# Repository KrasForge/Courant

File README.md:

# RADIAN

<p align="center">
  <a href="#listen"><b>Listen</b></a> ·
  <a href="#see-the-mesh-move"><b>See the mesh move</b></a> ·
  <a href="#the-hardware"><b>Hardware & 3D</b></a> ·
  <a href="#1-mathematical-foundation"><b>The maths</b></a> ·
  <a href="#4-architecture"><b>Architecture</b></a>
</p>

A 2D finite-difference physical-modeling synthesis engine in structural VHDL,
with an amplitude-dependent non-linear "chaos injection" term, playable
polyphonically over MIDI or CV.

Instead of recording or sampling an instrument, RADIAN solves the 2D acoustic
wave equation in real time on an FPGA mesh of arithmetic cells and streams the
result out as stereo audio: a vibrating drum head, a plate, a sheet of metal,
*computed* rather than recorded. A non-linear tension term makes the mesh
stiffen under load, so hard hits bend pitch upward and bloom into inharmonic,
metallic partials before settling into a natural decay. Notes arrive over MIDI
or control voltage, are allocated across independent polyphonic voices, and are
shaped by recallable instrument presets and a live front panel.

<sub>RADIAN was developed as **Courant**, which is why the repository and
some file paths still use that name.</sub>

> **Status: simulation-first, feature-complete in simulation, pre-hardware.**
> The engine, a Q1.23 reference model that is *bit-exact* to the RTL, and a full
> playable top (MIDI/CV $\rightarrow$ polyphony $\rightarrow$ I2S audio) are
> developed and verified under the current RTL regression across 31 testbenches. Board bring-up on a
> Digilent Arty A7 + Pmod I2S2 is the next step; nothing is claimed to work on
> hardware until it does.

---

## Listen

These clips come **out of the RTL**. A cycle-accurate Verilator build of
`synth_top` (4 voices, 8 $\times$ 8 mesh, 4$\times$ oversampling,
time-multiplexed) receives the score as bit-level serial MIDI at 31250 baud.
The note mapping, voice allocation, polyphonic meshes, mixer, DC blocker,
clock-domain crossing and I2S serialiser all run in it, and its 24-bit I2S
output is captured. Each clip gets one constant gain to peak at −1 dBFS. There
is no EQ, compression, reverb or editing. **They are not hardware
recordings**: the FPGA has not been brought up yet. Click a spectrogram or a ▶
link and the clip plays in your browser.

| Clip | What you hear | Listen |
| --- | --- | --- |
| **Gong Chorale** | A-minor chord progression on the gong preset. 3–4 voices ring into each other | [▶ `rtl_gong_chorale.mp3`](https://cdn.jsdelivr.net/gh/KrasForge/Courant@a1daff8e3a3599e712c28fc31fcfe1d983a12df5/docs/media/audio/rtl_gong_chorale.mp3) · 13 s |
| **Chaos Swell** | One held gong chord while CHAOS is turned up live over the control bus and back down | [▶ `rtl_chaos_swell.mp3`](https://cdn.jsdelivr.net/gh/KrasForge/Courant@a1daff8e3a3599e712c28fc31fcfe1d983a12df5/docs/media/audio/rtl_chaos_swell.mp3) · 12 s |
| **Plate Arpeggio** | Rolling pentatonic arpeggios on the plate preset with overlapping held notes, 112 BPM | [▶ `rtl_plate_arpeggio.mp3`](https://cdn.jsdelivr.net/gh/KrasForge/Courant@a1daff8e3a3599e712c28fc31fcfe1d983a12df5/docs/media/audio/rtl_plate_arpeggio.mp3) · 11 s |
| **Mallet Groove** | Marimba-like line on the damped drum preset over a held bass, 120 BPM | [▶ `rtl_mallet_groove.mp3`](https://cdn.jsdelivr.net/gh/KrasForge/Courant@a1daff8e3a3599e712c28fc31fcfe1d983a12df5/docs/media/audio/rtl_mallet_groove.mp3) · 10 s |
| **Berlin Voltage** | Dry EBM / industrial pulse, 132 BPM | [▶ `rtl_berlin_voltage.mp3`](https://cdn.jsdelivr.net/gh/KrasForge/Courant@f79031551d7316b354aa7c6243a771c9426d3952/docs/media/audio/rtl_berlin_voltage.mp3) · 10 s |
| **Oxide Dub** | Free-boundary metallic dub with long tails, 96 BPM | [▶ `rtl_oxide_dub.mp3`](https://cdn.jsdelivr.net/gh/KrasForge/Courant@f79031551d7316b354aa7c6243a771c9426d3952/docs/media/audio/rtl_oxide_dub.mp3) · 10 s |
| **Kreuz Rhythm** | Metallic polyrhythm with a tense finish, 150 BPM | [▶ `rtl_kreuz_rhythm.mp3`](https://cdn.jsdelivr.net/gh/KrasForge/Courant@f79031551d7316b354aa7c6243a771c9426d3952/docs/media/audio/rtl_kreuz_rhythm.mp3) · 10 s |

<sub>Rendered from the repaired RTL of 2026-09-16, the build behind
[`docs/sound_engine_repair.md`](docs/sound_engine_repair.md). It predates the
FX chain (drive, delay, chorus, reverb), the physical mallet and plate
stiffness, so these clips are the dry resonator. The scores are in
[`docs/media/scores/`](docs/media/scores/), and
[`make_scores.py`](docs/media/scripts/rtl/make_scores.py) writes the first
four. Rebuild the renderer from the
current RTL with
[`docs/media/scripts/rtl/build_renderer.sh`](docs/media/scripts/rtl/build_renderer.sh);
the whole 100 MHz system clock is simulated, so expect several minutes of CPU
per second of audio. Each clip also has an `.mp4` (spectrogram with a moving
playhead) in [`docs/media/audio/`](docs/media/audio/).</sub>

### Chaos off vs. chaos on

This one illustrates the non-linearity in the float reference model
([`model/NLMesh2D.m`](model/NLMesh2D.m), the same update as the RTL) on a
32 $\times$ 32 mesh. The same centre strike on the same gong mesh, first linear
($\alpha = 0$), then with chaos injection ($\alpha = 0.42$). The linear mesh
rings as a clean stack of fixed modes. With the amplitude-dependent term,
energy smears across the band right after the hit and the partials bend as the
mesh relaxes.

The flat ceiling near 5 kHz is not a filter. It is the highest mode a 2D
mesh can carry, $f_{\max} = \tfrac{f_s}{\pi}\arcsin(\gamma\sqrt{2}) \approx 4.9$ kHz
for this gong's $\gamma^2 = 0.05$. A finer mesh for the same pitch raises
$\gamma$ and lifts it.

### See the mesh move

The same hard strike on both meshes, slowed down about 800 $\times$. On the
left the wavefront spreads at one speed. On the right the loud centre
stiffens, so it runs ahead and breaks into fine, high-frequency ripples:
those ripples are the inharmonic partials you hear.

---

## The hardware

The engine targets a two-board desktop/Eurorack instrument. A 160 $\times$ 100 mm,
six-layer **Artix-7 mainboard** (FPGA, flash, clocks, PCM5102A DAC, CV/pot ADC,
opto-isolated MIDI) carries a **panel/interface board** 19.99 mm above it on
two 20-pin Samtec mezzanines. The panel has six knobs (TENSION · DECAY ·
CHAOS large, DRIVE · DELAY · REVERB small), a push encoder, the MODE switch,
four LEDs and five patch jacks. Neither board has been fabricated yet. See
[`hardware/CURRENT_DESIGN.md`](hardware/CURRENT_DESIGN.md) for what is and is
not validated.

<p align="center">
  <br>
  <sub>The two boards out of the case: the panel/interface board mated 19.99 mm above the Artix-7 mainboard.</sub>
</p>

<p align="center">
  <br>
  <sub>See-through view of the desktop case with both boards and the actual-part 3D models inside, rendered from
  the STEP assembly described in <a href="hardware/CURRENT_DESIGN.md"><code>hardware/CURRENT_DESIGN.md</code></a>
  (the STEP files themselves are not committed). The case has not been built yet.</sub>
</p>

| Mainboard (top) | Panel / interface board (front) |
| --- | --- |
|  |  |
|  |  |

<p align="center">
  <br>
  <sub>Side view of the stack. The mainboard's Samtec IPT1 posts reach into the panel's IPS1 sockets; the FPGA shows through the panel window.</sub>
</p>

**Open the 3D model:** [`courant_stack.stl`](docs/media/3d/courant_stack.stl)
opens in GitHub's built-in 3D viewer, so you can orbit it in the browser. The
coloured glTF files ([stack](docs/media/3d/courant_stack.glb),
[mainboard](docs/media/3d/courant_mainboard.glb),
[panel](docs/media/3d/courant_panel.glb)) open in any glTF viewer, Blender, or
https://gltf-viewer.donmccurdy.com.

<sub>Every outline, drill, pad, track and component position is read straight
from the native KiCad 10 boards. Component bodies are simplified parametric
stand-ins sized from package datasheets, and the knobs are illustrative. The
full actual-part STEP assembly lives outside the repo, so treat these as
layout previews, not mechanical CAD. Regenerate everything with
[`docs/media/scripts/make_media.sh`](docs/media/scripts/make_media.sh).</sub>

---

## Why an FPGA

A 2D mesh is embarrassingly parallel: every node runs the *same* small update
every time step, reading only its four neighbours. That maps naturally onto FPGA
fabric, where many nodes update concurrently and the per-sample cost does not
grow the way a sequential `for`-loop over the grid does on a CPU.

The honest trade is real, and this README states it plainly rather than selling
a fantasy:

| Aspect | Software (CPU / plugin) | This FPGA engine |
| --- | --- | --- |
| **Grid scaling** | Sequential per node; cost grows with node count | Concurrent nodes; one mesh step per audio sample, independent of node count (up to the fabric's DSP/LUT budget) |
| **Latency** | Governed by the host audio buffer (roughly 0.7 to 6 ms typical) | Deterministic, sub-sample; no block buffering. Group delay through the model is the physical wave propagation itself |
| **Per-node non-linearity** | Often simplified or dropped to save CPU | Evaluated on every node, every step |
| **Iteration speed** | Edit, recompile in seconds | Requires re-synthesis (minutes); behaviour bounded by chosen fabric |
| **Cost / footprint** | Runs on hardware you already own | Needs an FPGA plus an audio codec; each extra voice consumes finite DSP/LUT |

FPGAs win on **deterministic parallelism and latency**. Software wins on
**flexibility and cost**. This project is about the former.

---

## 1. Mathematical foundation

The engine models a lossy 2D wave equation for the transverse displacement
$u(x, y, t)$ of the surface:

$$\frac{\partial^2 u}{\partial t^2} = c^2\left(\frac{\partial^2 u}{\partial x^2} + \frac{\partial^2 u}{\partial y^2}\right) - 2\sigma\frac{\partial u}{\partial t}$$

- $c$ is the wave propagation speed (sets pitch and tension);
- $\sigma$ is the frequency-independent damping (sets decay time).

### Discretisation

Using centred finite differences on a grid with spacing $h$ and time step
$k = 1/f_s$ (with $f_s$ the audio rate, e.g. 48 kHz), the explicit update for
node $(i, j)$ is:

$$u_{i,j}^{n+1} = \frac{1}{1+\sigma k}\left[\,2u_{i,j}^{n} - (1-\sigma k)\,u_{i,j}^{n-1} + \gamma^2\left(u_{i+1,j}^{n} + u_{i-1,j}^{n} + u_{i,j+1}^{n} + u_{i,j-1}^{n} - 4u_{i,j}^{n}\right)\right]$$

where $\gamma = ck/h$ is the **Courant number**. The bracketed Laplacian stencil
is the only inter-node coupling; everything else is local. In the RTL the two
damping coefficients are precomputed on the control bus,

$$a_0 = \frac{1}{1+\sigma k}, \qquad \mathrm{sigk1} = 1 - \sigma k,$$

so no node ever performs a division (division is expensive in fabric; this
avoids it entirely).

### Stability (CFL), and why it is the whole game here

An explicit 2D scheme is only stable when the Courant number satisfies

$$\gamma^2 \le \tfrac{1}{2}\qquad\left(\gamma \le \tfrac{1}{\sqrt 2}\approx 0.7071\right).$$

Cross that line and the scheme does not merely "sound bad," it diverges
**exponentially**. This constraint governs every design decision in the next
section.

---

## 2. The non-linear twist: chaos injection

A linear mesh with a constant $\gamma$ is predictable and, frankly, a bit
sterile. RADIAN makes the local Courant term **amplitude-dependent**, so the
mesh stiffens where it is moving hardest:

$$\gamma_{i,j}^2 = \gamma_0^2 + \alpha\,(u_{i,j}^{n})^2$$

- $\gamma_0^2$ is the base stiffness and pitch;
- $\alpha$ is the chaos coupling.

High-amplitude regions momentarily raise the local wave speed, bending the
wavefront, shifting pitch up, and bleeding energy into inharmonic partials. This
is the characteristic "tension modulation" of struck plates and gongs, including
genuine period-doubling routes into chaos.

### The catch (and the fix)

The term $\alpha u^2$ only ever *increases* $\gamma^2$, and it does so hardest
exactly when the sound is loudest, pushing toward the CFL boundary precisely when
you least want it to. Naively, a hard hit drives $\gamma^2 > 1/2$ and the mesh
blows up. **Output saturation alone does not save you**: it clamps the
*displayed* sample while the internal state pins to the rails and buzzes at
Nyquist. You get a brick, not a gong.

The fix is structural, and is treated here as a first-class part of the design
rather than an afterthought:

1. **Clamp the local term:**
   $\gamma^2_{i,j} = \mathrm{clamp}(\gamma_0^2 + \alpha u^2,\ 0,\ \gamma^2_{\max})$
   with $\gamma^2_{\max} < 1/2$ (a safety margin below the CFL limit). This
   bounds the instability into a limit-cycle / soft-clip regime that is chaotic
   and rich, but convergent.
2. **Saturating state arithmetic:** displacement is clamped to the Q1.23 range,
   turning blow-up energy into musical soft saturation instead of wrap-around.
3. **Guaranteed decay:** the damping term $\sigma$ ensures the linear regime
   always returns to rest.

### Aliasing, stated rather than hidden

A squaring non-linearity at the base sample rate generates harmonics above
Nyquist that fold back as aliasing. "Zero aliasing" would be a false claim for
any non-linear scheme. The mitigation is **oversampling**: run the mesh at an
integer multiple of $f_s$ (the FPGA has ample clock headroom) and decimate on
output. The oversampling factor `OS` is a documented quality / area knob, not
magic; see [`docs/oversampling.md`](docs/oversampling.md).

---

## 3. Numerics

| Property | Value |
| --- | --- |
| Format | Signed **Q1.23** (24-bit two's complement) |
| Range / resolution | $[-1.0, +1.0)$ / $2^{-23}\approx 1.19\times 10^{-7}$ |
| Multiply | Q1.23 $\times$ Q1.23 gives Q2.46, rescaled by a `>>23` shift with round-to-nearest, saturated |
| Accumulation | Wide 48-bit guard accumulator, saturated on store |
| Coefficients | $a_0$ and $\mathrm{sigk1}$ precomputed on the control bus, so there is no per-node division |
| Overflow | Saturating arithmetic throughout: graceful soft-clip, never wrap-around spikes |

All fixed-point helpers (`sat_q123`, the rounding multiply, the clamp) live in
[`src/rtl/fdtd_pkg.vhd`](src/rtl/fdtd_pkg.vhd) and are exercised bit-for-bit
against the reference model (section 6).

---

## 4. Architecture

```
 MIDI / CV --> note mapping --.                     .--> I2S TX --> codec (DAC)
                              v                     |
   preset bank --> coeffs --> poly voices (N meshes + mix) --> CDC --> (audio clk)
                              ^                     |
        panel knobs/encoder --'   sample strobe <--'  (I2S word clock -> frame)
```

### Node Processing Element (PE)

Each node ([`node_element.vhd`](src/rtl/node_element.vhd)) owns:

- **State registers** holding $u^n$ and $u^{n-1}$;
- **A pipelined Q1.23 datapath** for the update above (Laplacian, the
  $\alpha u^2$ term, the $\gamma^2_{\max}$ clamp, the bracket, and the $a_0$
  scale), mapped to DSP slices;
- **Nearest-neighbour wiring** (N/S/E/W). Edge nodes use **fixed** ($u = 0$,
  Dirichlet) or **free** (mirrored, Neumann) boundaries.

### Spatial vs. time-multiplexed: the real engineering choice

A *fully spatial* mesh instantiates one PE per node. That is $O(N^2)$ DSP slices
and hits a hard ceiling fast: a 32$\times$32 mesh with a couple of multipliers
per node is well over a thousand DSPs, beyond most mid-range parts. The two
honest options, selected at synthesis time via the `mesh` wrapper and the
`TIME_MUX` generic:

- **Fully spatial** ([`grid_mesh.vhd`](src/rtl/grid_mesh.vhd)): small mesh on a
  large FPGA. Lowest latency, biggest area.
- **Time-multiplexed** ([`grid_mesh_tdm.vhd`](src/rtl/grid_mesh_tdm.vhd)): fold
  the grid through a single shared PE. At 100 MHz over 48 kHz there are roughly
  2083 system-clock cycles per audio sample, plenty to sweep a modest grid
  through one pipeline and still finish within a sample period. This costs
  ~18 DSP per voice *independent of grid size*, and it is the only way
  polyphony fits a small device.

Same RTL, a synthesis-time trade, documented per target in
[`docs/resource_budget.md`](docs/resource_budget.md).

### "Single cycle" and "zero latency": what is actually true

The per-node update is a multi-stage pipeline (multiplies, the clamp, the final
scale), not a single combinational clock edge. What *is* true:

- **One mesh time-step per audio sample:** the mesh advances on each sample
  strobe;
- **No audio-buffer latency:** there is no DAW block to fill, so end-to-end
  latency is sub-sample and deterministic, dominated by the codec and the PE
  pipeline depth (nanoseconds to microseconds), not milliseconds.

### Clocking and clock-domain crossings

The design spans two clock domains:

| Domain | Clock | Contents |
| --- | --- | --- |
| System | `sys_clk` (e.g. 100 MHz) | MIDI/CV front-ends, preset bank, polyphony (the mesh) |
| Audio | I2S `bclk` (divided from `mclk`) | I2S transceiver |

[`i2s_clkgen.vhd`](src/rtl/i2s_clkgen.vhd) makes the FPGA the **I2S master**:
from an audio master clock `mclk` (e.g. 12.288 MHz from an MMCM) it generates
MCLK / BCLK / LRCLK for the codec. [`sample_strobe.vhd`](src/rtl/sample_strobe.vhd)
crosses LRCLK back into `sys_clk` as the per-frame pulse that advances the mesh
one step per audio sample. Only two data crossings exist, both verified
primitives: a two-flop synchroniser on the async serial MIDI input, and the
stereo pickup word crossing `sys_clk` $\rightarrow$ `bclk` through
[`cdc_word.vhd`](src/rtl/cdc_word.vhd) (an MCP handshake). See
[`docs/cdc.md`](docs/cdc.md).

---

## 5. Playability

The engine is wrapped into a complete, flashable instrument
([`synth_top.vhd`](src/rtl/synth_top.vhd), board wrapper
[`syn/vivado/arty_synth.vhd`](syn/vivado/arty_synth.vhd)).

- **MIDI** ([`midi_frontend.vhd`](src/rtl/midi_frontend.vhd) over
  [`midi_uart_rx.vhd`](src/rtl/midi_uart_rx.vhd)): parses the 31250-baud serial
  stream, maps note number through a discrete-mesh calibrated pitch table, and
  maps velocity to strike amplitude only. CHAOS is an independent panel/CV
  control. See [`docs/midi.md`](docs/midi.md).
- **Control voltage** ([`cv_frontend.vhd`](src/rtl/cv_frontend.vhd)): the same note-mapping interface, driven from 1V/oct pitch, a gate, and a mod CV. MIDI/CV arbitration is normally automatic: the newest MIDI note-on or CV gate edge claims the source. Presets/registers can force MIDI or CV, while the legacy `cv_sel` port remains only as a force-CV/debug override. See [`docs/cv.md`](docs/cv.md).
- **Polyphony** ([`poly_voices.vhd`](src/rtl/poly_voices.vhd) +
  [`voice_allocator.vhd`](src/rtl/voice_allocator.vhd)): allocates each note to
  a free voice, runs `NVOICES` independent meshes, and averages their stereo
  pickups. With `TIME_MUX` the voices fold onto shared PEs so polyphony fits a
  small part. See [`docs/polyphony.md`](docs/polyphony.md).
- **Presets** ([`preset_bank.vhd`](src/rtl/preset_bank.vhd)): supplies TENSION, DECAY, CHAOS, the CFL clamp, **STIFFNESS / plate dispersion**, **HARDNESS / stateful physical mallet**, pickup geometry, RIM compliance, STRIKE SIZE/X/Y, MATERIAL/ANISO/CHARACTER and source override. Voice-relevant settings are latched into each newly struck voice. See [`docs/presets.md`](docs/presets.md).
- **Front panel** ([`panel_ctrl.vhd`](src/rtl/panel_ctrl.vhd)): the existing MODE switch is PLAY/EDIT. PLAY keeps TENSION/DECAY/CHAOS/DRIVE/DELAY/REVERB and encoder preset navigation; EDIT reuses the encoder to select soft-takeover parameter pages, with SURFACE currently mapping ANISO/RIM/STRIKE SIZE/STRIKE X/STRIKE Y/CHARACTER. The four LEDs show voices in PLAY and the selected page in EDIT. No new pot, ADC channel, connector or PCB signal is required. See [`docs/panel.md`](docs/panel.md).

The end-to-end path (MIDI/CV $\rightarrow$ note mapping $\rightarrow$ preset
merge $\rightarrow$ polyphonic meshes $\rightarrow$ CDC $\rightarrow$ I2S) is
described in [`docs/synth_top.md`](docs/synth_top.md).
The 2026-09-16 musical calibration/quality repair and acceptance results are in [`docs/sound_engine_repair.md`](docs/sound_engine_repair.md).

---

## 6. The reference model (bit-exact)

[`model/`](model/) holds a MATLAB/Octave reference implementation used both to
explore the physics and to *lock the RTL numerically*. The linear
([`Mesh2D.m`](model/Mesh2D.m)), stiff ([`StiffMesh2D.m`](model/StiffMesh2D.m)),
spatially-varying ([`VarMesh2D.m`](model/VarMesh2D.m)) and non-linear
([`NLMesh2D.m`](model/NLMesh2D.m)) meshes each have a study script (stability,
chaos, exciters, oversampling, materials). Crucially,
[`nl_reference.m`](model/nl_reference.m) regenerates the legacy nonlinear Q1.23 golden trace, while [`stiffness_reference.py`](model/stiffness_reference.py) and [`mallet_reference.py`](model/mallet_reference.py) independently regenerate the production fixed-point STIFFNESS and physical-mallet/HARDNESS traces. Their testbenches replay those traces step for step, so the corresponding hardware paths are verified **bit-exact** to independent models rather than merely "close." [`demo_render.m`](model/demo_render.m) renders musical, nonlinear, polyphonic demo audio.

---

## 7. Repository structure

```text
src/
  rtl/     Q1.23 package + node PE, spatial & time-mux meshes and selector,
           I2S transceiver + master clock gen + sample strobe, cdc_word,
           MIDI + CV front-ends, voice allocator + polyphony, preset bank,
           panel controller, control bus, synth_top (the playable design)
  tb/      31 RTL testbenches: unit (node, fdtd_pkg, i2s, cdc, uart, mallet) ->
           bit-exact golden traces (nl_mesh, mesh_impulse, boundary, pickup) ->
           end-to-end audio (synth_top, poly, preset_top, latency)
model/     MATLAB/Octave reference model (bit-exact to the RTL) + physics
           studies (stability, chaos, stiffness, spatial, exciters) + demos
sim/       GHDL Makefile: `make -C sim` analyses and runs the whole suite
syn/       yosys (open-source resource estimate) and Vivado (sign-off) flows,
           the Arty A7 + Pmod I2S2 constraints, and the board wrapper arty_synth
docs/      derivations, fixed-point + CFL analysis, per-feature notes
           (midi, cv, polyphony, presets, panel, cdc, oversampling, timing),
           the resource budget, and a deviations log
  media/   README sound demos, spectrograms, board renders, 3D models (.glb/.stl)
           and the scripts that regenerate them from model/ and hardware/
hardware/  native KiCad 10 mainboard (courant/) and panel/interface board
           (panel/), the shared direct-stack contract (stack/)
```

---

## 8. Building & simulating

The reference flow uses **GHDL** (open-source, VHDL-2008):

```sh
make -C sim                      # analyse + elaborate + run all 31 testbenches
octave-cli --eval "demo_render"  # render nonlinear polyphonic demo audio (model/)
docs/media/scripts/rtl/build_renderer.sh build  # cycle-accurate RTL audio renderer (Verilator)
docs/media/scripts/make_media.sh # regenerate README audio, spectrograms, PCB renders, 3D models
cd syn/yosys && ./report_util.sh # DSP / LUT / FF resource estimate (yosys)
```

A single unit test can be run directly, e.g.

```sh
ghdl -a --std=08 src/rtl/fdtd_pkg.vhd src/rtl/node_element.vhd src/tb/node_element_tb.vhd
ghdl -r --std=08 node_element_tb --wave=sim/node.ghw
```

---

## 9. Target hardware and resources

Synthesis targets a low-cost dev board for bring-up: a **Digilent Arty A7**
(Xilinx Artix-7) with a **Pmod I2S2** codec, keeping the path to real audio
cheap and reproducible. The FPGA is the I2S master; the constraints live in
[`syn/vivado/arty_synth.xdc`](syn/vivado/arty_synth.xdc). The Vivado non-project
flow ([`build_synth.tcl`](syn/vivado/build_synth.tcl)) runs opt/place/route and
fails the build on negative slack (a pass/fail timing gate).

Beyond the dev board there is a **standalone instrument PCB** — a 160 x 100 mm
six-layer board carrying an XC7A50T, its configuration flash, both oscillators,
a PCM5102A stereo DAC, and the analog front end the Arty build leaves off (panel
pots and CV over an MCP3208, an opto-isolated MIDI input, a gate comparator).
It started in [tscircuit](https://tscircuit.com) and is now maintained as native
KiCad 10 boards in [`hardware/courant/`](hardware/courant/) (mainboard) and
[`hardware/panel/`](hardware/panel/) (panel/interface board); every device
pinout is checked against its manufacturer datasheet and the FPGA ball map
against AMD's own package file. Both boards are **fully routed but never
fabricated**: the mainboard has 2158 track segments, 4386 mm of copper and 299
vias, and KiCad DRC reports 0 violations / 0 unconnected on both boards. See
[`hardware/CURRENT_DESIGN.md`](hardware/CURRENT_DESIGN.md) and
[`docs/board.md`](docs/board.md) for what is and is not verified.

Using the time-multiplexed mesh (~18 DSP per voice, independent of grid size),
resources scale roughly linearly with voice count:

| Voices | DSP48 | LUT | Fits |
| --- | --- | --- | --- |
| 1 | ~24 | ~8.6k | A7-35T |
| 2 | ~38 | ~15.6k | A7-35T |
| 4 | ~74 | ~30.4k | A7-35T (90 DSP) |
| 8 | ~146 | ~61.6k | A7-100T (240 DSP) |

Numbers are from the open-source yosys flow; the yosys LUT figures are
pessimistic (a combinational-read mesh memory maps to LUT mux-trees, where
Vivado would infer LUTRAM/BRAM). Full table and caveats in
[`docs/resource_budget.md`](docs/resource_budget.md).

---

## 10. What this is and is not

- It **is** a deterministic, low-latency, parallel physical-modeling engine and
  an honest study of non-linear FDTD on FPGA, playable over MIDI and CV.
- It **is** simulation-first: nothing is claimed to "work on hardware" until it
  has. The RTL, the reference model, and the full playable top are complete and
  verified in simulation.
- It is **not** zero-latency, zero-aliasing, or single-clock-cycle. Those are
  marketing, and this document avoids them deliberately.
- It is **not** yet a hardware product. The standalone boards are routed and
  pass DRC, and the MCP3208 SPI reader for the panel / CV ADC
  ([`adc_mcp3208.vhd`](src/rtl/adc_mcp3208.vhd)) passes its testbench, but
  nothing has been fabricated or brought up yet.

---

## License

MIT.

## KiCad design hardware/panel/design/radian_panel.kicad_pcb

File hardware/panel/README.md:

# RADIAN / PANEL P1 — direct-stack six-control revision

**One panel/interface PCB for the RADIAN FPGA mainboard. Engineering prototype; native electrical/PCB checks are clean, but physical hardware validation is still required.**

| Front (F.Cu) | Back (B.Cu, faces the mainboard) |
| --- | --- |
|  |  |

<sub>Rendered from `design/radian_panel.kicad_pcb` by `docs/media/scripts/`. Component bodies in the 3D view are simplified stand-ins and the knobs are illustrative. See `docs/media/README.md`.</sub>

Open `design/radian_panel.kicad_pro` with KiCad 10 and keep the project-local symbols/footprints with it. The authoritative panel PCB passes native ERC, DRC, filled-zone connectivity and schematic/PCB parity with zero findings. Current review fabrication outputs are in `fab/` and `radian_panel-fab.zip`.

## Current architecture
- Four-layer panel PCB, 1.6 mm thick, about 180.5 × 108 mm, with DIN/ventilation reliefs.
- Six Bourns 10 kOhm pots: **TENSION · DECAY · CHAOS · DRIVE · DELAY · REVERB**.
- Push encoder, MODE switch, four LEDs and five vertical mono patch jacks.
- Rack +12 V and desktop 12 V feed the panel converter; the mainboard still receives regulated VIN5.
- Rack input remains a 10-pin module-side Eurorack connector; −12 V is unused.
- Default MOD bypass preserves the original unipolar behavior; the optional bipolar MOD path still requires firmware calibration.
- PITCH scaling and stereo line-level outputs are unchanged.

## Direct panel-to-mainboard connection
The old J101…J116 cable-header bundle is retired. The boards now connect directly through two 2×10, 2.54 mm mezzanine pairs:
- **J17 main ↔ J100 panel:** Samtec IPT1-110-06-L-D ↔ IPS1-110-01-L-D, carrying VIN5/GND/VREF25, six pot wipers, CV/gate and stereo audio.
- **J18 main ↔ J101 panel:** the same Samtec pair, carrying 3V3/GND, encoder, MODE, LEDs, MIDI, PROGRAM/RESET and JTAG.

The shared source of truth is `../stack/panel-stack.json`. It specifies 19.99 mm fully mated spacing, 20.45 mm maximum spacing and a ~20.0 mm support-stack target. Standoffs/supports carry structural load; the connectors are not structural fasteners.

The final native boards have 40/40 mating pins matched by net and assembled XY, with 1.02 mm mainboard drills and 1.04 mm panel drills. Exact connector MPNs are present in both BOMs. Real connector seating, retention and enclosure tolerance still require a physical first article.

## Case / enclosure
The retained desktop/Eurorack enclosure has been revised to match this panel. The old three macro holes are closed, six current control locations are present, MODE moves to (154, 57) mm, and the old raised MODE insert becomes the REVERB insert. The mainboard/support plane is shifted 0.46 mm for the 19.99 mm fully-mated Samtec stack. See `cad/RADIAN_P1_desktop_fit_study.step` and `reports/CASE_UPDATE.md`.

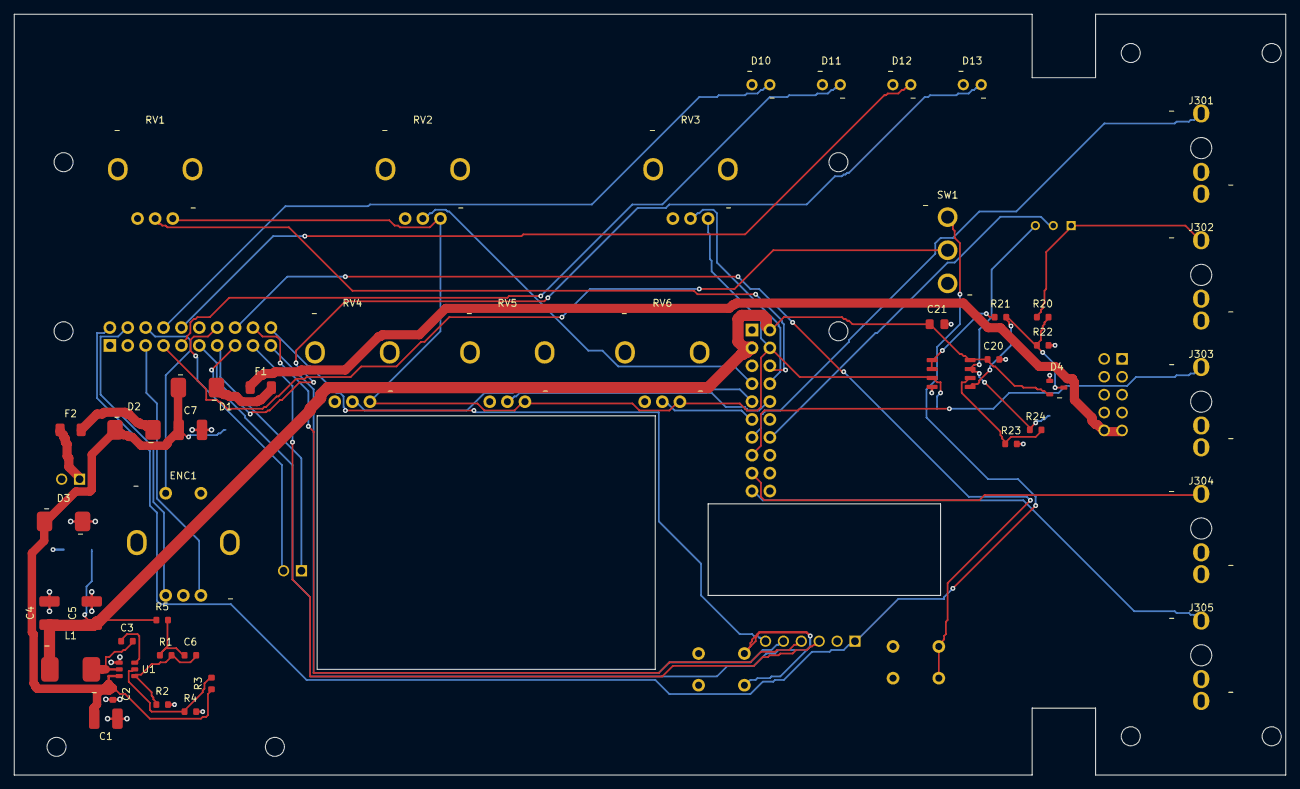
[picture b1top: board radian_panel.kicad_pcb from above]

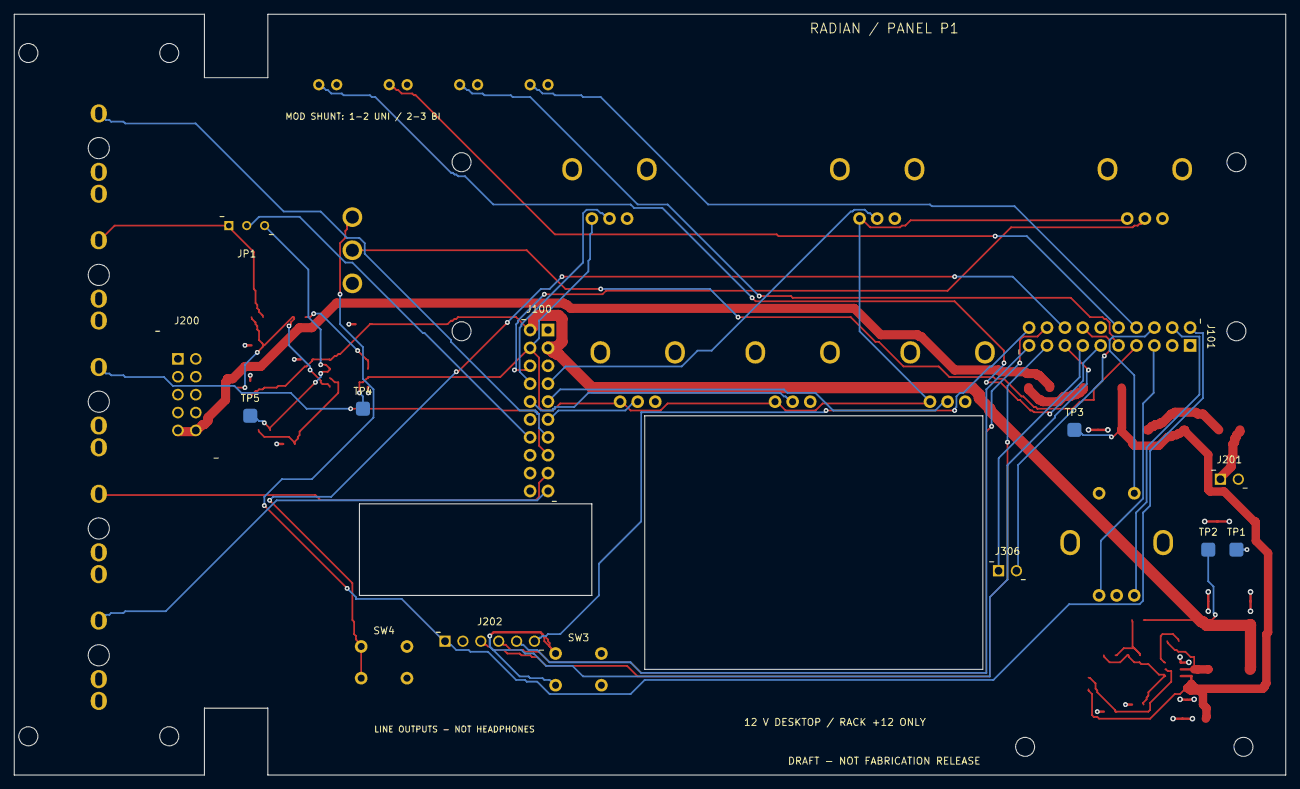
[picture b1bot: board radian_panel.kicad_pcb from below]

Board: 4 copper layers, 180.5 x 108.0 mm, 59 parts (14 on the bottom side), 46 nets.

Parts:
C1, C7: 10uF; C_1210
C2, C3, C20: 100nF; C_0603
C4, C5: 22uF; C_1210
C6: 75pF; C_0603
C21: 1uF; C_0805
D1, D2: SS54 / OR; D_SMB
D3: SMBJ15A; D_SMB
D4: BAT54S; SOT23_BAT54S
D10: VOICE 1; LED_D3.0_P2.54
D11: VOICE 2; LED_D3.0_P2.54
D12: VOICE 3; LED_D3.0_P2.54
D13: VOICE 4; LED_D3.0_P2.54
ENC1: 24 PPR / PUSH; Bourns_PEC11R4_RearFacing_Switch
F1, F2: 2A FUSE / >=32V; Fuse_1206
J100, J101: IPS1-110-01-L-D; Stack_2x10_P2.54
J200: 61201021621; Wurth_61201021621_Exact_B
J201: 22-27-2021; Molex_22-27-2021_J201_B
J202: 22-27-2061; Molex_22-27-2061_J202_B
J301: PITCH 0-5V; WQP518MA_PJ398SM_Vertical
J302: MOD; WQP518MA_PJ398SM_Vertical
J303: GATE; WQP518MA_PJ398SM_Vertical
J304: LINE L; WQP518MA_PJ398SM_Vertical
J305: LINE R; WQP518MA_PJ398SM_Vertical
J306: 22-27-2021; Molex_22-27-2021_J306_B
JP1: 450301014042; Wurth_450301014042_Exact_B
L1: 10uH 4A / Isat7.5A; Bourns_SRP7050TA
R1, R21: 100k; R_0603
R2: 13.3k; R_0603
R3: 511k; R_0603
R4: 105k; R_0603
R5: 49.9; R_0603
R20, R22: 200k; R_0603
R23, R24: 10k; R_0603
RV1: 10k linear / TENSION; Bourns_PTV09A4_RearFacing
RV2: 10k linear / DECAY; Bourns_PTV09A4_RearFacing
RV3: 10k linear / CHAOS; Bourns_PTV09A4_RearFacing
RV4: 10k linear / DRIVE; Bourns_PTV09A4_RearFacing
RV5: 10k linear / DELAY; Bourns_PTV09A4_RearFacing
RV6: 10k linear / REVERB; Bourns_PTV09A4_RearFacing
SW1: MODE / SPDT ON-ON; E_Switch_100SP_M2
SW3: PROGRAM / SERVICE; SW_PUSH_6x6_P6.5x4.5
SW4: RESET / SERVICE; SW_PUSH_6x6_P6.5x4.5
TP1: GND; TestPoint_D2
TP2: VIN5; TestPoint_D2
TP3: VRAW; TestPoint_D2
TP4: VREF25; TestPoint_D2
TP5: MOD_BIPOLAR; TestPoint_D2
U1: TPS54302DDCR; TI_DDC0006A_SOT23_6
U2: OPA2192ID; SOIC8_3.9x4.9_P1.27

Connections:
BOOT: C3.1, U1.6
DESKTOP_12V: F2.1, J201.1
DESKTOP_FUSED: D2.2, F2.2
EN: R3.2, R4.1, U1.5
ENC_A_RAW: ENC1.A, J101.4
ENC_B_RAW: ENC1.B, J101.5
ENC_SW_RAW: ENC1.S1, J101.6
FB: C6.2, R1.2, R2.1, U1.4
FF_TOP: C6.1, R1.1, R5.2
GATE_IN: J100.15, J303.3
GND: C1.2, C2.2, C4.2, C5.2, C7.2, C20.2, C21.2, D3.2, D4.1, D10.1, D11.1, D12.1, D13.1, ENC1.C, ENC1.S2, J100.1, J100.5, J100.12, J100.16, J100.18, J100.20, J101.1, J101.3, J101.12, J200.3, J200.4, J200.5, J200.6, J200.7, J200.8, J201.2, J202.2, J301.1, J301.2, J302.1, J302.2, J303.1, J303.2, J304.1, J305.1, R2.2, R4.2, R22.2, R23.2, RV1.1, RV2.1, RV3.1, RV4.1, RV5.1, RV6.1, SW1.1, SW3.2, SW4.2, TP1.1, U1.1, U2.4
JTAG_TCK: J101.17, J202.3
JTAG_TDI: J101.19, J202.5
JTAG_TDO: J101.18, J202.4
JTAG_TMS: J101.20, J202.6
LED0_A: D10.2, J101.8
LED1_A: D11.2, J101.9
LED2_A: D12.2, J101.10
LED3_A: D13.2, J101.11
LINE_L: J100.17, J304.3
LINE_R: J100.19, J305.3
MIDI4: J101.13, J306.1
MIDI5: J101.14, J306.2
MOD_BIPOLAR: JP1.2, R24.1, TP5.1, U2.7
MOD_FB: R23.1, R24.2, U2.6
MOD_IN: J100.14, JP1.1
MOD_RAW: J302.3, JP1.3, R20.1
MOD_SUM: D4.3, R20.2, R21.2, R22.1, U2.5
PITCH_IN: J100.13, J301.3
POT_DECAY_RAW: J100.7, RV2.2
POT_DELAY_RAW: J100.10, RV5.2
POT_DRIVE_RAW: J100.9, RV4.2
POT_PITCH_RAW: J100.6, RV1.2
POT_REVERB_RAW: J100.11, RV6.2
POT_TIMBRE_RAW: J100.8, RV3.2
PROGRAM_B: J101.15, SW3.1
RACK_12V: F1.1, J200.9, J200.10
RACK_FUSED: D1.2, F1.2
SW: C3.2, L1.2, U1.2
V3V3: J101.2, J202.1, SW1.3
VIN5: C4.1, C5.1, C20.1, C21.1, D4.2, J100.2, J100.3, L1.1, R5.1, TP2.1, U2.8
VRAW: C1.1, C2.1, C7.1, D1.1, D2.1, D3.1, R3.1, TP3.1, U1.3
VREF25: J100.4, RV1.3, RV2.3, RV3.3, RV4.3, RV5.3, RV6.3, TP4.1, U2.3
VREF_BUF: R21.1, U2.1, U2.2
cv_select: J101.7, SW1.2
reset_n: J101.16, SW4.1

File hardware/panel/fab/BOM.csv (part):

Reference,Value,Manufacturer,MPN_or_selection_gate,Footprint,Side,X_panel_mm,Y_panel_mm,DNP,Notes
J100,IPS1-110-01-L-D,Samtec,IPS1-110-01-L-D,RadianPanel:Stack_2x10_P2.54,B,124.0,61.75,False,Direct mezzanine A; Samtec IPS1 socket mates mainboard IPT1-110-06-L-D. Fully-mated PCB gap 19.99 mm; max 20.45 mm. Use ~20.0 mm standoffs and bench-verify seating before production quantity.
J101,IPS1-110-01-L-D,Samtec,IPS1-110-01-L-D,RadianPanel:Stack_2x10_P2.54,B,43.0,72.25,False,Direct mezzanine B; Samtec IPS1 socket mates mainboard IPT1-110-06-L-D. Fully-mated PCB gap 19.99 mm; max 20.45 mm. Use ~20.0 mm standoffs and bench-verify seating before production quantity.
RV1,10k linear / TENSION,Bourns,PTV09A-4020F-B103,RadianPanel:Bourns_PTV09A4_RearFacing,F,38.0,96.0,False,"Pin 1 CCW/GND, pin 3 CW/VREF25: verify direction on physical sample. No added wiper RC. Mount tabs soldered, electrically NC."
RV2,10k linear / DECAY,Bourns,PTV09A-4020F-B103,RadianPanel:Bourns_PTV09A4_RearFacing,F,76.0,96.0,False,"Pin 1 CCW/GND, pin 3 CW/VREF25: verify direction on physical sample. No added wiper RC. Mount tabs soldered, electrically NC."
RV3,10k linear / CHAOS,Bourns,PTV09A-4020F-B103,RadianPanel:Bourns_PTV09A4_RearFacing,F,114.0,96.0,False,"Pin 1 CCW/GND, pin 3 CW/VREF25: verify direction on physical sample. No added wiper RC. Mount tabs soldered, electrically NC."
RV4,10k linear / DRIVE,Bourns,PTV09A-4020F-B103,RadianPanel:Bourns_PTV09A4_RearFacing,F,66.0,70.0,False,"Pin 1 CCW/GND, pin 3 CW/VREF25: verify direction on physical sample. No added wiper RC. Mount tabs soldered, electrically NC."
RV5,10k linear / DELAY,Bourns,PTV09A-4020F-B103,RadianPanel:Bourns_PTV09A4_RearFacing,F,88.0,70.0,False,"Pin 1 CCW/GND, pin 3 CW/VREF25: verify direction on physical sample. No added wiper RC. Mount tabs soldered, electrically NC."
RV6,10k linear / REVERB,Bourns,PTV09A-4020F-B103,RadianPanel:Bourns_PTV09A4_RearFacing,F,110.0,70.0,False,"Pin 1 CCW/GND, pin 3 CW/VREF25: verify direction on physical sample. No added wiper RC. Mount tabs soldered, electrically NC."
ENC1,24 PPR / PUSH,Bourns,PEC11R-4220F-S0024,RadianPanel:Bourns_PEC11R4_RearFacing_Switch,F,42.0,43.0,False,20 mm shaft / 7 mm bushing replaces proposed 15 mm shaft part to accommodate common PCB plane. Check encoder direction and nut stack.
SW1,MODE / SPDT ON-ON,E-Switch,100SP1T1B1M2REH,RadianPanel:E_Switch_100SP_M2,F,150.5,84.5,False,"Gold contact option for low-level logic. ST110001 mechanical M2 pattern, 4.7 mm pitch. R contact selection from manufacturer configurator; purchase/stack validation required."
D10,VOICE 1,Kingbright,L-934GD,RadianPanel:LED_D3.0_P2.54,F,124.0,108.0,False,"3 mm LED, anode pad 2, cathode pad 1. Mainboard already has series resistor. Set flange height with assembly jig; envelope is not seated LED height."
D11,VOICE 2,Kingbright,L-934GD,RadianPanel:LED_D3.0_P2.54,F,134.0,108.0,False,"3 mm LED, anode pad 2, cathode pad 1. Mainboard already has series resistor. Set flange height with assembly jig; envelope is not seated LED height."
D12,VOICE 3,Kingbright,L-934GD,RadianPanel:LED_D3.0_P2.54,F,144.0,108.0,False,"3 mm LED, anode pad 2, cathode pad 1. Mainboard already has series resistor. Set flange height with assembly jig; envelope is not seated LED height."
D13,VOICE 4,Kingbright,L-934GD,RadianPanel:LED_D3.0_P2.54,F,154.0,108.0,False,"3 mm LED, anode pad 2, cathode pad 1. Mainboard already has series resistor. Set flange height with assembly jig; envelope is not seated LED height."
J301,PITCH 0-5V,QingPu / Thonk,WQP518MA (Thonkiconn/PJ398SM),RadianPanel:WQP518MA_PJ398SM_Vertical,F,186.5,99.0,False,"Vertical mono, grounded normal for inputs only. Sleeve=1, switched contact=2, tip=3. Imported supplier dimension drawing needs sample fit check."
J302,MOD,QingPu / Thonk,WQP518MA (Thonkiconn/PJ398SM),RadianPanel:WQP518MA_PJ398SM_Vertical,F,186.5,81.0,False,"Vertical mono, grounded normal for inputs only. Sleeve=1, switched contact=2, tip=3. Imported supplier dimension drawing needs sample fit check."
J303,GATE,QingPu / Thonk,WQP518MA (Thonkiconn/PJ398SM),RadianPanel:WQP518MA_PJ398SM_Vertical,F,186.5,63.0,False,"Vertical mono, grounded normal for inputs only. Sleeve=1, switched contact=2, tip=3. Imported supplier dimension drawing needs sample fit check."
J304,LINE L,QingPu / Thonk,WQP518MA (Thonkiconn/PJ398SM),RadianPanel:WQP518MA_PJ398SM_Vertical,F,186.5,45.0,False,"Vertical mono, grounded normal for inputs only. Sleeve=1, switched contact=2, tip=3. Imported supplier dimension drawing needs sample fit check."
J305,LINE R,QingPu / Thonk,WQP518MA (Thonkiconn/PJ398SM),RadianPanel:WQP518MA_PJ398SM_Vertical,F,186.5,27.0,False,"Vertical mono, grounded normal for inputs only. Sleeve=1, switched contact=2, tip=3. Imported supplier dimension drawing needs sample fit check."
J306,22-27-2021,Molex,22-27-2021,RadianPanel:Molex_22-27-2021_J306_B,B,57.5,39.0,False,Exact KK-254 2-circuit friction-lock header to retained Same Sky SDS-50J MIDI DIN pins 4 and 5. No DIN 2/shield-to-GND connection.
J200,61201021621,Wurth Elektronik,61201021621,RadianPanel:Wurth_61201021621_Exact_B,B,174.0,64.0,False,"Exact keyed WR-BHD 2x5 2.54 mm header. Module-side 10-pin: 1/2=-12 NC, 3-8=GND, 9/10=+12. Use 16-to-10 cable to bus. Red stripe at pins 1/2; verify both cable ends. No bus +5/CV/gate connections."
J201,22-27-2021,Molex,22-27-2021,RadianPanel:Molex_22-27-2021_J201_B,B,26.0,52.0,False,Exact KK-254 2-circuit friction-lock header from the chassis-mounted 12 V DC inlet. NOT a 5 V inlet.
F1,2A FUSE / >=32V,,SELECT 2 A >=32 V 1206 fuse,RadianPanel:Fuse_1206,F,53.0,65.0,False,"Final fuse MPN, surge rating, derating and TVS coordination are an explicit release gate."
F2,2A FUSE / >=32V,,SELECT 2 A >=32 V 1206 fuse,RadianPanel:Fuse_1206,F,26.0,59.0,False,"Final fuse MPN, surge rating, derating and TVS coordination are an explicit release gate."
D1,SS54 / OR,Vishay,SS54-E3/57T,RadianPanel:D_SMB,F,44.0,65.0,False,"Pad 1 cathode VRAW, pad 2 anode fused source. Diode OR, no priority, shared ground. Measure worst-case diode temperature."
D2,SS54 / OR,Vishay,SS54-E3/57T,RadianPanel:D_SMB,F,35.0,59.0,False,"Pad 1 cathode VRAW, pad 2 anode fused source. Diode OR, no priority, shared ground. Measure worst-case diode temperature."
D3,SMBJ15A,Vishay,SMBJ15A-E3/52,RadianPanel:D_SMB,F,25.0,46.0,False,Unidirectional input TVS. Verify source fault energy and fuse coordination before any fault test.
U1,TPS54302DDCR,Texas Instruments,TPS54302DDCR,RadianPanel:TI_DDC0006A_SOT23_6,F,34.0,25.0,False,"3 A IC rating is a design target, not validated system delivery. TI March 2026 datasheet 5 V reference circuit."
L1,10uH 4A / Isat7.5A,Bourns,SRP7050TA-100M,RadianPanel:Bourns_SRP7050TA,F,26.0,25.0,False,4 A Irms / 7.5 A Isat at stated datasheet conditions; temperature rise needs testing.
C1,10uF,,SELECT 10uF 50V X7R 1210,RadianPanel:C_1210,F,31.0,18.0,False,50V X7R; verify effective capacitance at DC bias
C2,100nF,,SELECT 100nF 50V X7R 0603,RadianPanel:C_0603,F,32.0,21.5,False,50V X7R; verify effective capacitance at DC bias
C3,100nF,,SELECT 100nF 16V X7R 0603,RadianPanel:C_0603,F,34.0,29.0,False,16V X7R; verify effective capacitance at DC bias
C4,22uF,,SELECT 22uF 25V X7R 1210,RadianPanel:C_1210,F,23.0,33.0,False,25V X7R; verify effective capacitance at DC bias
C5,22uF,,SELECT 22uF 25V X7R 1210,RadianPanel:C_1210,F,29.0,33.0,False,25V X7R; verify effective capacitance at DC bias
R1,100k,,SELECT 100k 1% 0603,RadianPanel:R_0603,F,39.5,27.0,False,Resistor 1%
R2,13.3k,,SELECT 13.3k 1% 0603,RadianPanel:R_0603,F,39.0,20.0,False,Resistor 1%
R3,511k,,SELECT 511k 1% 0603,RadianPanel:R_0603,F,46.0,23.0,False,Resistor 1%
R4,105k,,SELECT 105k 1% 0603,RadianPanel:R_0603,F,43.0,19.0,False,Resistor 1%
R5,49.9,,SELECT 49.9 1% 0603,RadianPanel:R_0603,F,39.0,32.0,False,Resistor 1%
C6,75pF,,SELECT 75pF 50V C0G 0603,RadianPanel:C_0603,F,43.0,27.0,False,50V C0G; verify effective capacitance at DC bias
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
